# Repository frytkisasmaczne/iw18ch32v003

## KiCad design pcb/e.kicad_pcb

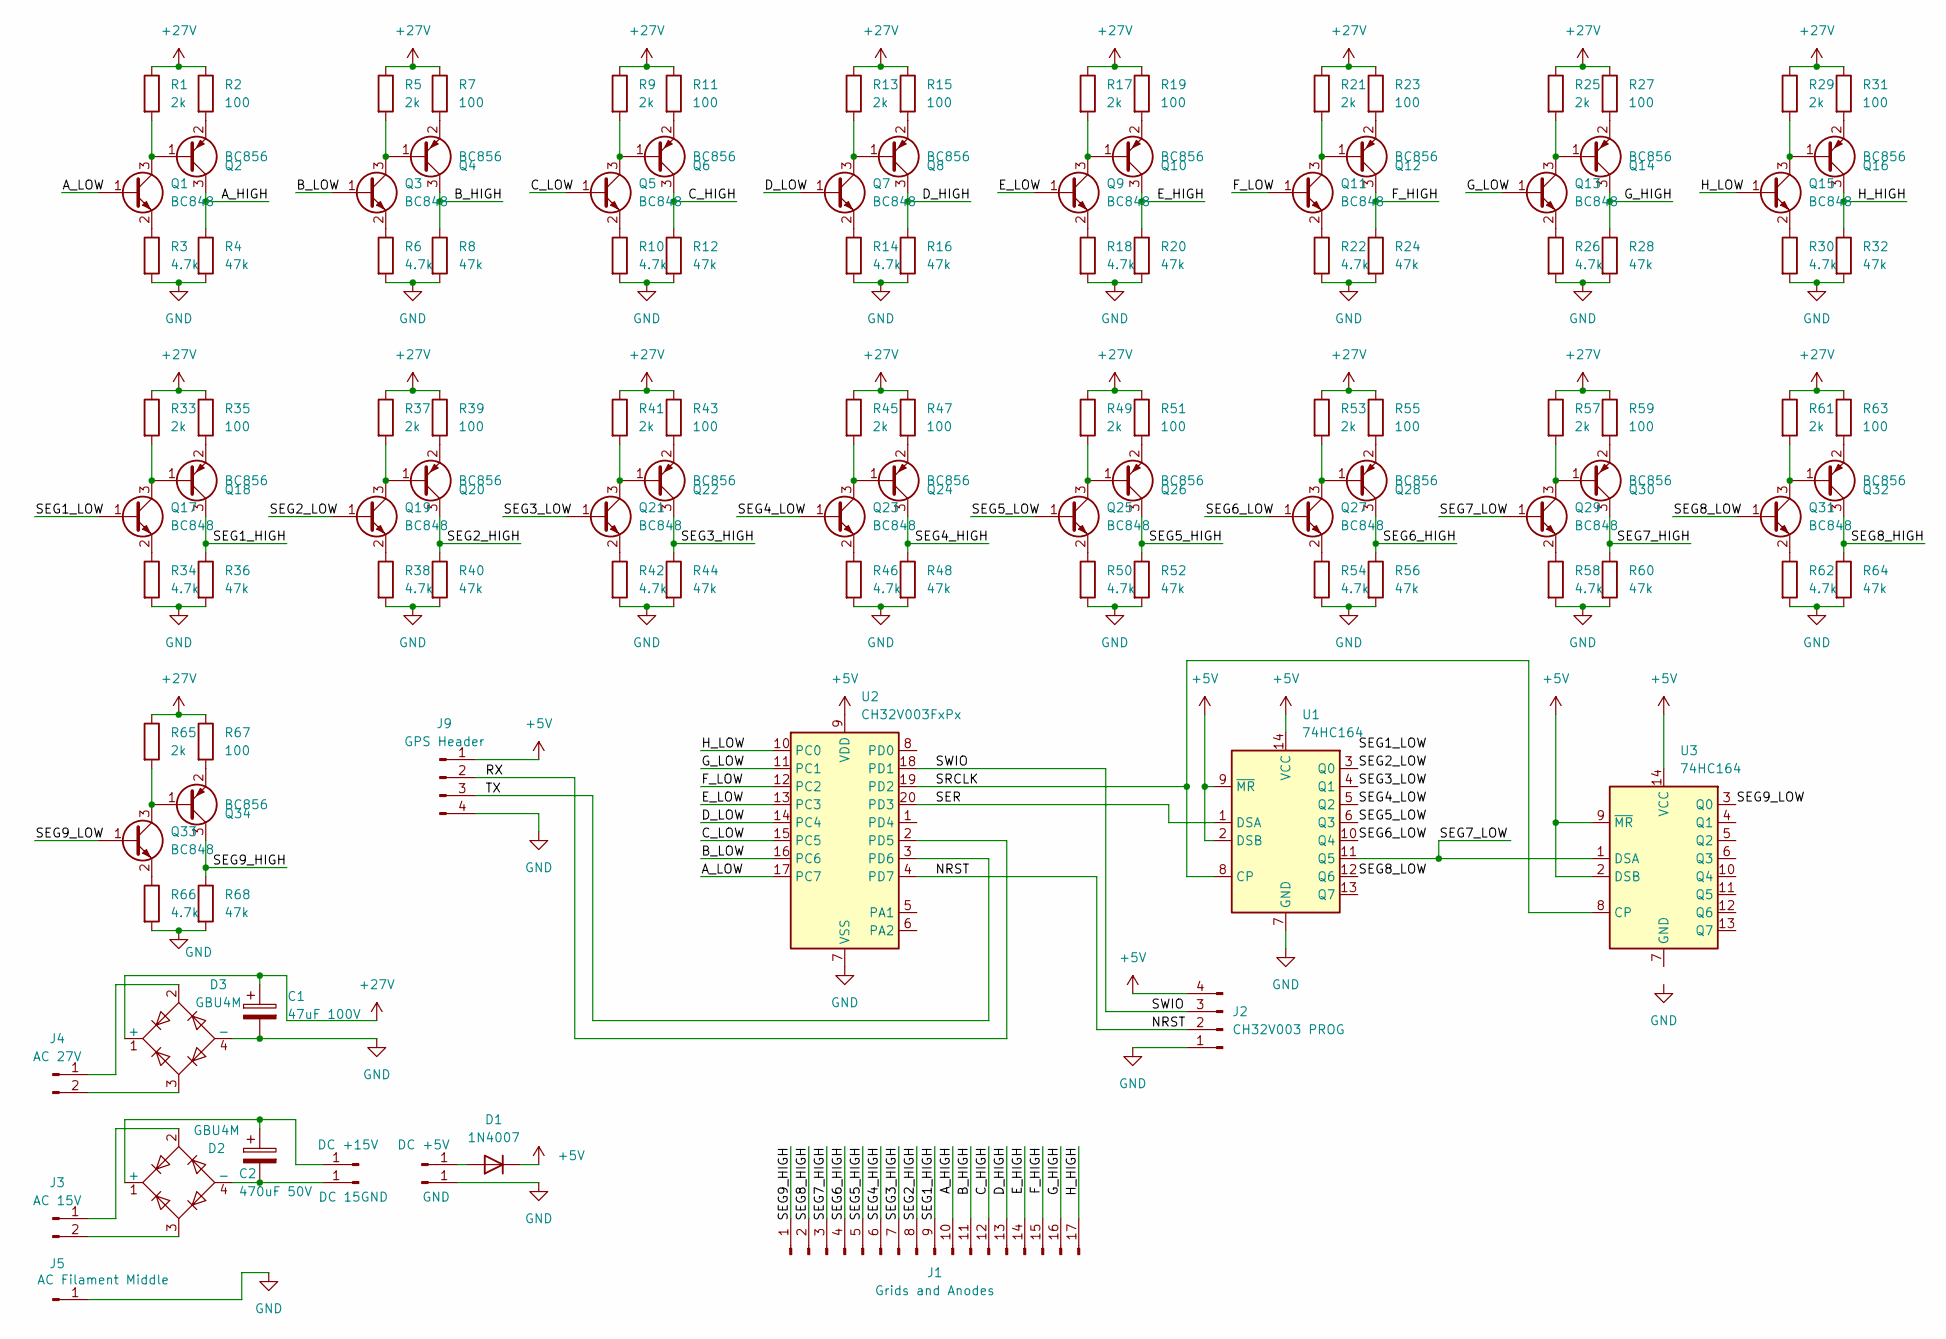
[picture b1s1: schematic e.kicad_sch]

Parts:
C1: 47uF 100V; CP_Radial_D10.0mm_P5.00mm
C2: 470uF 50V; CP_Radial_D13.0mm_P5.00mm
D1: 1N4007; D_DO-41_SOD81_P10.16mm_Horizontal
D2, D3: GBU4M; Diode_Bridge_Vishay_GBU
J1: Grids and Anodes; PinHeader_1x17_P2.54mm_Vertical
J2: CH32V003 PROG; PinHeader_1x04_P2.54mm_Vertical
J3: AC 15V; PinHeader_1x02_P2.54mm_Vertical
J4: AC 27V; PinHeader_1x02_P2.54mm_Vertical
J5: AC Filament Middle; PinHeader_1x01_P2.54mm_Vertical
J6: DC +15V; PinHeader_1x01_P2.54mm_Vertical
J7: DC 15GND; PinHeader_1x01_P2.54mm_Vertical
J8: DC +5V; PinHeader_1x01_P2.54mm_Vertical
J9: GPS Header; PinHeader_1x04_P2.54mm_Vertical
J10: GND; PinHeader_1x01_P2.54mm_Vertical
Q1, Q3, Q5, Q7, Q9, Q11, Q13, Q15, Q17, Q19, Q21, Q23, Q25, Q27, Q29, Q31, Q33: BC848; SOT-23
Q2, Q4, Q6, Q8, Q10, Q12, Q14, Q16, Q18, Q20, Q22, Q24, Q26, Q28, Q30, Q32, Q34: BC856; SOT-23
R1, R5, R9, R13, R17, R21, R25, R29, R33, R37, R41, R45, R49, R53, R57, R61, R65: 2k; R_0201_0603Metric
R2, R7, R11, R15, R19, R23, R27, R31, R35, R39, R43, R47, R51, R55, R59, R63, R67: 100; R_0201_0603Metric
R3, R6, R10, R14, R18, R22, R26, R30, R34, R38, R42, R46, R50, R54, R58, R62, R66: 4.7k; R_0201_0603Metric
R4, R8, R12, R16, R20, R24, R28, R32, R36, R40, R44, R48, R52, R56, R60, R64, R68: 47k; R_0201_0603Metric
U1, U3: 74HC164; SSOP-14_5.3x6.2mm_P0.65mm
U2: CH32V003FxPx; TSSOP-20_4.4x6.5mm_P0.65mm

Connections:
+5V: D1.1 (K), J2.4, J9.1, U1.2 (DSB), U1.9 (~MR), U1.14 (VCC), U2.9 (VDD), U3.2 (DSB), U3.9 (~MR), U3.14 (VCC)
+27V: C1.1, D3.1 (+), R1.1, R2.1, R5.1, R7.1, R9.1, R11.1, R13.1, R15.1, R17.1, R19.1, R21.1, R23.1, R25.1, R27.1, R29.1, R31.1, R33.1, R35.1, R37.1, R39.1, R41.1, R43.1, R45.1, R47.1, R49.1, R51.1, R53.1, R55.1, R57.1, R59.1, R61.1, R63.1, R65.1, R67.1
/A_HIGH: J1.10, Q2.3 (C), R4.1
/A_LOW: Q1.1 (B), U2.17 (PC7)
/B_HIGH: J1.11, Q4.3 (C), R8.1
/B_LOW: Q3.1 (B), U2.16 (PC6)
/C_HIGH: J1.12, Q6.3 (C), R12.1
/C_LOW: Q5.1 (B), U2.15 (PC5)
/D_HIGH: J1.13, Q8.3 (C), R16.1
/D_LOW: Q7.1 (B), U2.14 (PC4)
/E_HIGH: J1.14, Q10.3 (C), R20.1
/E_LOW: Q9.1 (B), U2.13 (PC3)
/F_HIGH: J1.15, Q12.3 (C), R24.1
/F_LOW: Q11.1 (B), U2.12 (PC2)
/G_HIGH: J1.16, Q14.3 (C), R28.1
/G_LOW: Q13.1 (B), U2.11 (PC1)
/H_HIGH: J1.17, Q16.3 (C), R32.1
/H_LOW: Q15.1 (B), U2.10 (PC0)
/NRST: J2.2, U2.4 (PD7)
/RX: J9.2, U2.2 (PD5)
/SEG1_HIGH: J1.9, Q18.3 (C), R36.1
/SEG1_LOW: Q17.1 (B)
/SEG2_HIGH: J1.8, Q20.3 (C), R40.1
/SEG2_LOW: Q19.1 (B), U1.3 (Q0)
/SEG3_HIGH: J1.7, Q22.3 (C), R44.1
/SEG3_LOW: Q21.1 (B), U1.4 (Q1)
/SEG4_HIGH: J1.6, Q24.3 (C), R48.1
/SEG4_LOW: Q23.1 (B), U1.5 (Q2)
/SEG5_HIGH: J1.5, Q26.3 (C), R52.1
/SEG5_LOW: Q25.1 (B), U1.6 (Q3)
/SEG6_HIGH: J1.4, Q28.3 (C), R56.1
/SEG6_LOW: Q27.1 (B), U1.10 (Q4)
/SEG7_HIGH: J1.3, Q30.3 (C), R60.1
/SEG7_LOW: Q29.1 (B), U1.11 (Q5), U3.1 (DSA)
/SEG8_HIGH: J1.2, Q32.3 (C), R64.1
/SEG8_LOW: Q31.1 (B), U1.12 (Q6)
/SEG9_HIGH: J1.1, Q34.3 (C), R68.1
/SEG9_LOW: Q33.1 (B), U3.3 (Q0)
/SER: U1.1 (DSA), U2.20 (PD3)
/SRCLK: U1.8 (CP), U2.19 (PD2), U3.8 (CP)
/SWIO: J2.3, U2.18 (PD1)
/TX: J9.3, U2.3 (PD6)
GND: C1.2, D3.4 (-), J2.1, J5.1, J9.4, J10.1, R3.2, R4.2, R6.2, R8.2, R10.2, R12.2, R14.2, R16.2, R18.2, R20.2, R22.2, R24.2, R26.2, R28.2, R30.2, R32.2, R34.2, R36.2, R38.2, R40.2, R42.2, R44.2, R46.2, R48.2, R50.2, R52.2, R54.2, R56.2, R58.2, R60.2, R62.2, R64.2, R66.2, R68.2, U1.7 (GND), U2.7 (VSS)
unnamed: D1.2 (A), J8.1
unnamed: C2.1, D2.1 (+), J6.1
unnamed: C2.2, D2.4 (-), J7.1
unnamed: D2.2, J3.1
unnamed: D2.3, J3.2
unnamed: D3.2, J4.1
unnamed: D3.3, J4.2
unnamed: Q1.3 (C), Q2.1 (B), R1.2
unnamed: Q1.2 (E), R3.1
unnamed: Q2.2 (E), R2.2
unnamed: Q3.3 (C), Q4.1 (B), R5.2
unnamed: Q3.2 (E), R6.1
unnamed: Q4.2 (E), R7.2
unnamed: Q5.3 (C), Q6.1 (B), R9.2
unnamed: Q5.2 (E), R10.1
unnamed: Q6.2 (E), R11.2
unnamed: Q7.3 (C), Q8.1 (B), R13.2
unnamed: Q7.2 (E), R14.1
unnamed: Q8.2 (E), R15.2
unnamed: Q9.2 (E), R18.1
unnamed: Q9.3 (C), Q10.1 (B), R17.2
unnamed: Q10.2 (E), R19.2
unnamed: Q11.3 (C), Q12.1 (B), R21.2
unnamed: Q11.2 (E), R22.1
unnamed: Q12.2 (E), R23.2
unnamed: Q13.3 (C), Q14.1 (B), R25.2
unnamed: Q13.2 (E), R26.1
unnamed: Q14.2 (E), R27.2
unnamed: Q15.3 (C), Q16.1 (B), R29.2
unnamed: Q15.2 (E), R30.1
unnamed: Q16.2 (E), R31.2
unnamed: Q17.3 (C), Q18.1 (B), R33.2
unnamed: Q17.2 (E), R34.1
unnamed: Q18.2 (E), R35.2
unnamed: Q19.3 (C), Q20.1 (B), R37.2
unnamed: Q19.2 (E), R38.1
unnamed: Q20.2 (E), R39.2
unnamed: Q21.3 (C), Q22.1 (B), R41.2
unnamed: Q21.2 (E), R42.1
unnamed: Q22.2 (E), R43.2
unnamed: Q23.3 (C), Q24.1 (B), R45.2
unnamed: Q23.2 (E), R46.1
unnamed: Q24.2 (E), R47.2
unnamed: Q25.3 (C), Q26.1 (B), R49.2
unnamed: Q25.2 (E), R50.1
unnamed: Q26.2 (E), R51.2
unnamed: Q27.3 (C), Q28.1 (B), R53.2
unnamed: Q27.2 (E), R54.1
unnamed: Q28.2 (E), R55.2
unnamed: Q29.3 (C), Q30.1 (B), R57.2
unnamed: Q29.2 (E), R58.1
unnamed: Q30.2 (E), R59.2
unnamed: Q31.3 (C), Q32.1 (B), R61.2
unnamed: Q31.2 (E), R62.1
unnamed: Q32.2 (E), R63.2
unnamed: Q33.3 (C), Q34.1 (B), R65.2
unnamed: Q33.2 (E), R66.1
unnamed: Q34.2 (E), R67.2

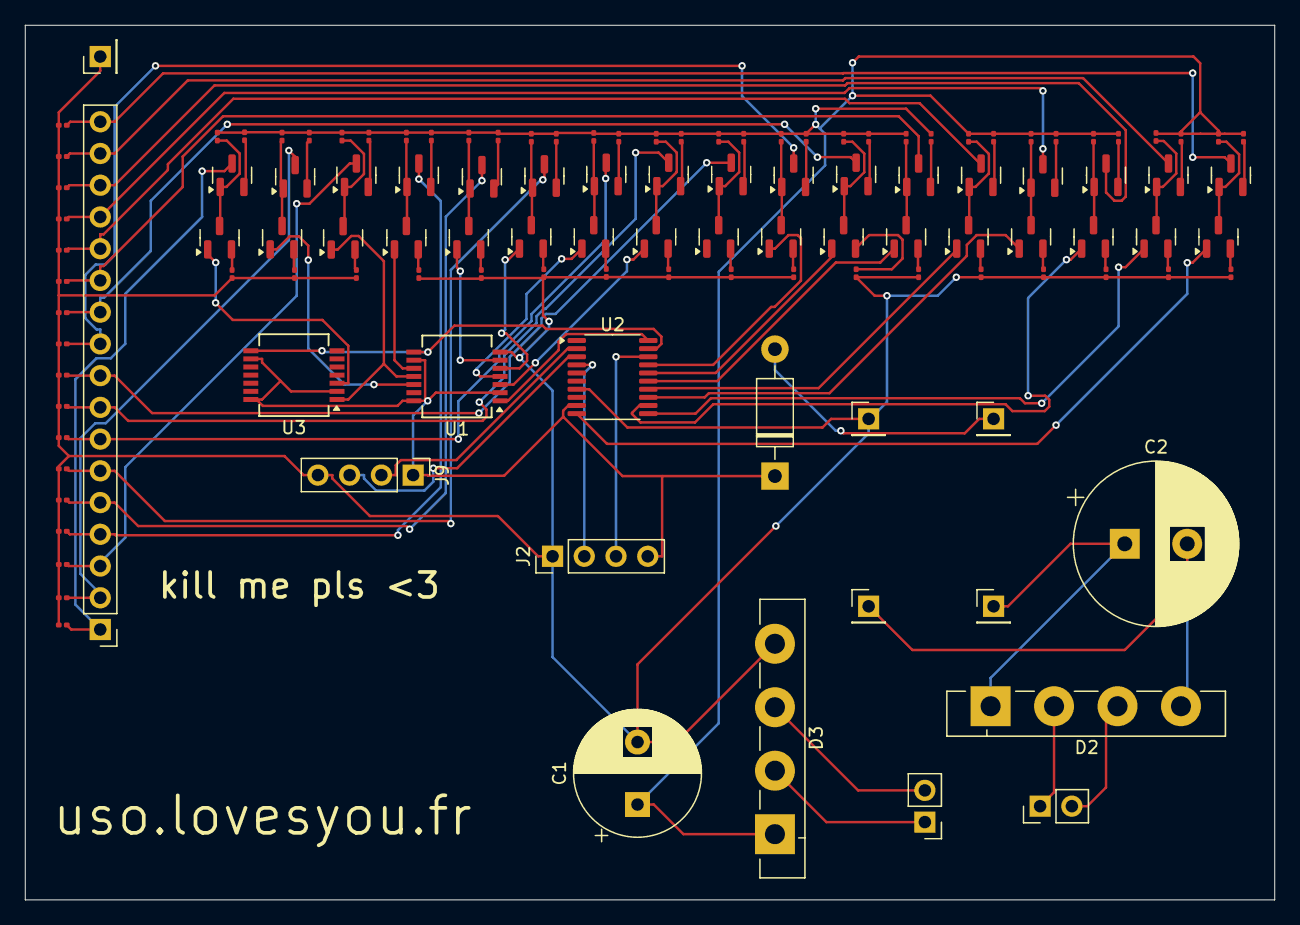
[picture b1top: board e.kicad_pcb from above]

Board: 2 copper layers, 100.0 x 70.0 mm, 120 parts (0 on the bottom side), 100 nets.

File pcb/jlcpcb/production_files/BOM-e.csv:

Comment,Designator,Footprint,LCSC,Quantity
GND,J10,PinHeader_1x01_P2.54mm_Vertical,,1
DC +5V,J8,PinHeader_1x01_P2.54mm_Vertical,,1
DC 15GND,J7,PinHeader_1x01_P2.54mm_Vertical,,1
DC +15V,J6,PinHeader_1x01_P2.54mm_Vertical,,1
BC848,Q13,SOT-23,,1
BC856,Q20,SOT-23,,1
BC848,Q23,SOT-23,,1
470uF 50V,C2,CP_Radial_D13.0mm_P5.00mm,,1
4.7k,R62,R_0201_0603Metric,,1
100,R23,R_0201_0603Metric,,1
47k,R40,R_0201_0603Metric,,1
100,R51,R_0201_0603Metric,,1
100,R11,R_0201_0603Metric,,1
2k,R13,R_0201_0603Metric,,1
BC848,Q31,SOT-23,,1
BC848,Q7,SOT-23,,1
BC856,Q30,SOT-23,,1
4.7k,R58,R_0201_0603Metric,,1
4.7k,R3,R_0201_0603Metric,,1
BC856,Q6,SOT-23,,1
Grids and Anodes,J1,PinHeader_1x17_P2.54mm_Vertical,,1
74HC164,U3,SSOP-14_5.3x6.2mm_P0.65mm,,1
GPS Header,J9,PinHeader_1x04_P2.54mm_Vertical,,1
100,R55,R_0201_0603Metric,,1
47k,R56,R_0201_0603Metric,,1
4.7k,R38,R_0201_0603Metric,,1
4.7k,R34,R_0201_0603Metric,,1
BC856,Q8,SOT-23,,1
4.7k,R14,R_0201_0603Metric,,1
BC848,Q33,SOT-23,,1
2k,R21,R_0201_0603Metric,,1
2k,R41,R_0201_0603Metric,,1
BC848,Q15,SOT-23,,1
4.7k,R6,R_0201_0603Metric,,1
2k,R9,R_0201_0603Metric,,1
AC 15V,J3,PinHeader_1x02_P2.54mm_Vertical,,1
BC856,Q22,SOT-23,,1
BC856,Q16,SOT-23,,1
2k,R37,R_0201_0603Metric,,1
BC848,Q1,SOT-23,,1
BC856,Q26,SOT-23,,1
4.7k,R10,R_0201_0603Metric,,1
47k,R60,R_0201_0603Metric,,1
CH32V003 PROG,J2,PinHeader_1x04_P2.54mm_Vertical,,1
BC856,Q4,SOT-23,,1
BC848,Q9,SOT-23,,1
BC856,Q32,SOT-23,,1
2k,R5,R_0201_0603Metric,,1
BC848,Q19,SOT-23,,1
2k,R1,R_0201_0603Metric,,1
100,R39,R_0201_0603Metric,,1
47k,R28,R_0201_0603Metric,,1
4.7k,R42,R_0201_0603Metric,,1
100,R19,R_0201_0603Metric,,1
BC856,Q12,SOT-23,,1
47k,R36,R_0201_0603Metric,,1
BC856,Q34,SOT-23,,1
100,R59,R_0201_0603Metric,,1
2k,R33,R_0201_0603Metric,,1
2k,R25,R_0201_0603Metric,,1
100,R31,R_0201_0603Metric,,1
4.7k,R22,R_0201_0603Metric,,1
100,R15,R_0201_0603Metric,,1
47k,R16,R_0201_0603Metric,,1
47k,R68,R_0201_0603Metric,,1
4.7k,R50,R_0201_0603Metric,,1
4.7k,R30,R_0201_0603Metric,,1
100,R67,R_0201_0603Metric,,1
100,R7,R_0201_0603Metric,,1
47k,R48,R_0201_0603Metric,,1
100,R27,R_0201_0603Metric,,1
BC856,Q28,SOT-23,,1
47k,R20,R_0201_0603Metric,,1
47k,R8,R_0201_0603Metric,,1
BC856,Q24,SOT-23,,1
AC Filament Middle,J5,PinHeader_1x01_P2.54mm_Vertical,,1
2k,R65,R_0201_0603Metric,,1
100,R2,R_0201_0603Metric,,1
47k,R32,R_0201_0603Metric,,1
BC848,Q5,SOT-23,,1
1N4007,D1,D_DO-41_SOD81_P10.16mm_Horizontal,,1
BC848,Q29,SOT-23,,1
47k,R52,R_0201_0603Metric,,1
100,R43,R_0201_0603Metric,,1
47k,R4,R_0201_0603Metric,,1
2k,R61,R_0201_0603Metric,,1
2k,R49,R_0201_0603Metric,,1
47k,R44,R_0201_0603Metric,,1
BC848,Q25,SOT-23,,1
100,R63,R_0201_0603Metric,,1
100,R47,R_0201_0603Metric,,1
47uF 100V,C1,CP_Radial_D10.0mm_P5.00mm,,1
BC848,Q11,SOT-23,,1
AC 27V,J4,PinHeader_1x02_P2.54mm_Vertical,,1
BC856,Q18,SOT-23,,1
74HC164,U1,SSOP-14_5.3x6.2mm_P0.65mm,,1
BC848,Q17,SOT-23,,1
2k,R53,R_0201_0603Metric,,1
4.7k,R54,R_0201_0603Metric,,1
CH32V003FxPx,U2,TSSOP-20_4.4x6.5mm_P0.65mm,,1
2k,R17,R_0201_0603Metric,,1
BC856,Q2,SOT-23,,1
4.7k,R18,R_0201_0603Metric,,1
47k,R12,R_0201_0603Metric,,1
2k,R57,R_0201_0603Metric,,1
4.7k,R26,R_0201_0603Metric,,1
BC848,Q21,SOT-23,,1
BC848,Q3,SOT-23,,1
2k,R29,R_0201_0603Metric,,1
BC856,Q10,SOT-23,,1
GBU4M,D2,Diode_Bridge_Vishay_GBU,,1
BC856,Q14,SOT-23,,1
4.7k,R46,R_0201_0603Metric,,1
4.7k,R66,R_0201_0603Metric,,1
100,R35,R_0201_0603Metric,,1
2k,R45,R_0201_0603Metric,,1
47k,R24,R_0201_0603Metric,,1
BC848,Q27,SOT-23,,1
47k,R64,R_0201_0603Metric,,1
GBU4M,D3,Diode_Bridge_Vishay_GBU,,1

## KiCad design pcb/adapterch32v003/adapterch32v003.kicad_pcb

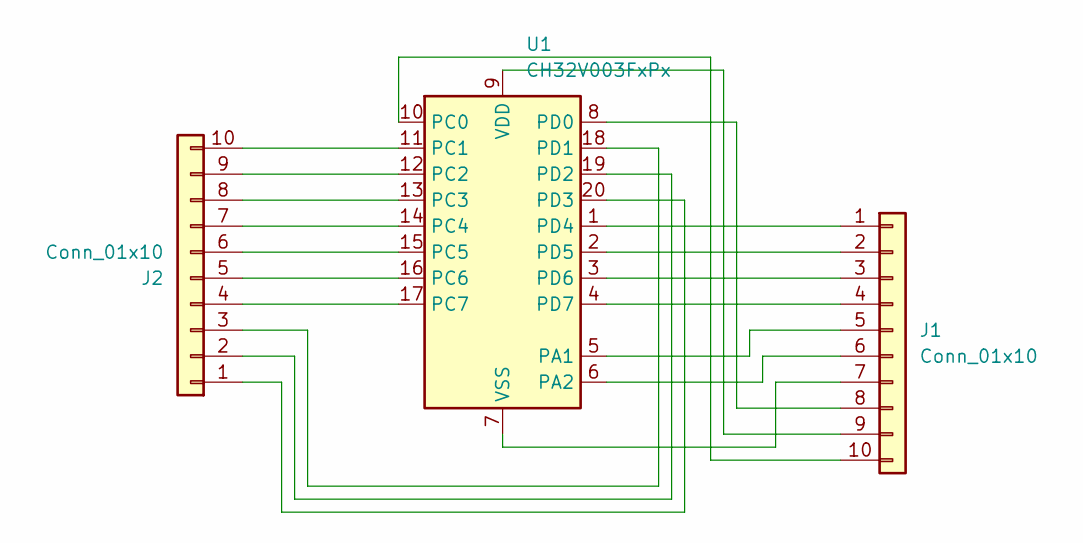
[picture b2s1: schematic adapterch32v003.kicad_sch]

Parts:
J1, J2: Conn_01x10; PinHeader_1x10_P2.54mm_Vertical
U1: CH32V003FxPx; TSSOP-20_4.4x6.5mm_P0.65mm

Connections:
unnamed: J1.1, U1.1 (PD4)
unnamed: J1.2, U1.2 (PD5)
unnamed: J1.3, U1.3 (PD6)
unnamed: J1.4, U1.4 (PD7)
unnamed: J1.5, U1.5 (PA1)
unnamed: J1.6, U1.6 (PA2)
unnamed: J1.7, U1.7 (VSS)
unnamed: J1.8, U1.8 (PD0)
unnamed: J1.9, U1.9 (VDD)
unnamed: J1.10, U1.10 (PC0)
unnamed: J2.1, U1.20 (PD3)
unnamed: J2.2, U1.19 (PD2)
unnamed: J2.3, U1.18 (PD1)
unnamed: J2.4, U1.17 (PC7)
unnamed: J2.5, U1.16 (PC6)
unnamed: J2.6, U1.15 (PC5)
unnamed: J2.7, U1.14 (PC4)
unnamed: J2.8, U1.13 (PC3)
unnamed: J2.9, U1.12 (PC2)
unnamed: J2.10, U1.11 (PC1)

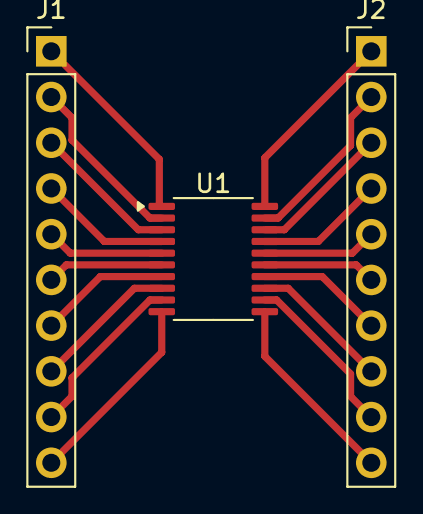
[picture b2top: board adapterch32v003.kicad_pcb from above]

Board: 2 copper layers, 3 parts (0 on the bottom side), 20 nets.

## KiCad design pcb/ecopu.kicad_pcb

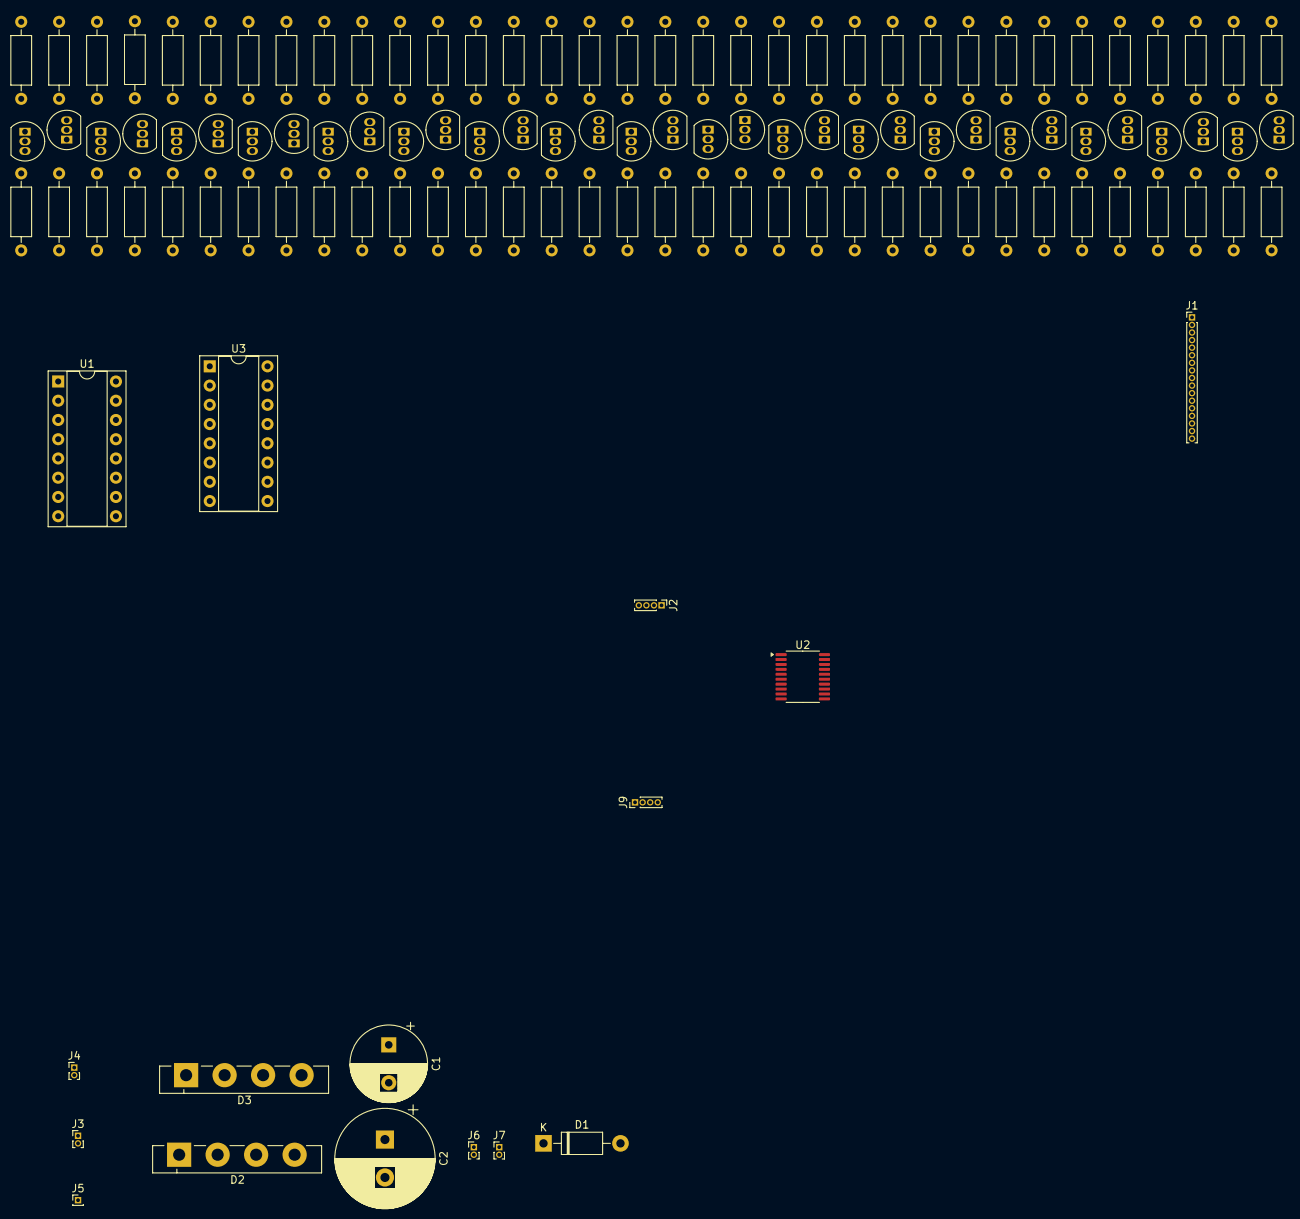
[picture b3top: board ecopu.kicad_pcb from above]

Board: 2 copper layers, 118 parts (0 on the bottom side), 101 nets, no tracks yet.

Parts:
C1: 47uF 100V; CP_Radial_D10.0mm_P5.00mm
C2: 470uF 50V; CP_Radial_D13.0mm_P5.00mm
D1: 1N4007; D_DO-41_SOD81_P10.16mm_Horizontal
D2, D3: GBU4M; Diode_Bridge_Vishay_GBU
J1: Grids and Anodes; PinHeader_1x17_P1.00mm_Vertical
J2: CH32V003 PROG; PinHeader_1x04_P1.00mm_Vertical
J3: AC 15V; PinHeader_1x02_P1.00mm_Vertical
J4: AC 27V; PinHeader_1x02_P1.00mm_Vertical
J5: AC Filament Middle; PinHeader_1x01_P1.00mm_Vertical
J6: Step-down IN; PinHeader_1x02_P1.00mm_Vertical
J7: Step-down OUT; PinHeader_1x02_P1.00mm_Vertical
J9: GPS Header; PinHeader_1x04_P1.00mm_Vertical
Q1, Q3, Q5, Q7, Q9, Q11, Q13, Q15, Q17, Q19, Q21, Q23, Q25, Q27, Q29, Q31, Q33: BC237; TO-92_Inline
Q2, Q4, Q6, Q8, Q10, Q12, Q14, Q16, Q18, Q20, Q22, Q24, Q26, Q28, Q30, Q32, Q34: BC307; TO-92_Inline
R1, R5, R9, R13, R17, R21, R25, R29, R33, R37, R41, R45, R49, R53, R57, R61, R65: 2k; R_Axial_DIN0207_L6.3mm_D2.5mm_P10.16mm_Horizontal
R2, R7, R11, R15, R19, R23, R27, R31, R35, R39, R43, R47, R51, R55, R59, R63, R67: 100; R_Axial_DIN0207_L6.3mm_D2.5mm_P10.16mm_Horizontal
R3, R6, R10, R14, R18, R22, R26, R30, R34, R38, R42, R46, R50, R54, R58, R62, R66: 4.7k; R_Axial_DIN0207_L6.3mm_D2.5mm_P10.16mm_Horizontal
R4, R8, R12, R16, R20, R24, R28, R32, R36, R40, R44, R48, R52, R56, R60, R64, R68: 47k; R_Axial_DIN0207_L6.3mm_D2.5mm_P10.16mm_Horizontal
U1, U3: 74HC595; DIP-16_W7.62mm_Socket
U2: CH32V003FxPx; TSSOP-20_4.4x6.5mm_P0.65mm

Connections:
+3.3V: D1.1 (K), U1.16 (VCC), U2.9 (VDD), U3.16 (VCC)
+5V: J2.4, J9.1, U1.10 (~SRCLR), U3.10 (~SRCLR)
+27V: C1.1, D3.1 (+), R1.1, R2.1, R5.1, R7.1, R9.1, R11.1, R13.1, R15.1, R17.1, R19.1, R21.1, R23.1, R25.1, R27.1, R29.1, R31.1, R33.1, R35.1, R37.1, R39.1, R41.1, R43.1, R45.1, R47.1, R49.1, R51.1, R53.1, R55.1, R57.1, R59.1, R61.1, R63.1, R65.1, R67.1
/A_HIGH: J1.10, Q2.1 (C), R4.1
/A_LOW: Q1.2 (B), U2.17 (PC7)
/B_HIGH: J1.11, Q4.1 (C), R8.1
/B_LOW: Q3.2 (B), U2.16 (PC6)
/C_HIGH: J1.12, Q6.1 (C), R12.1
/C_LOW: Q5.2 (B), U2.15 (PC5)
/D_HIGH: J1.13, Q8.1 (C), R16.1
/D_LOW: Q7.2 (B), U2.14 (PC4)
/E_HIGH: J1.14, Q10.1 (C), R20.1
/E_LOW: Q9.2 (B), U2.13 (PC3)
/F_HIGH: J1.15, Q12.1 (C), R24.1
/F_LOW: Q11.2 (B), U2.12 (PC2)
/G_HIGH: J1.16, Q14.1 (C), R28.1
/G_LOW: Q13.2 (B), U2.11 (PC1)
/H_HIGH: J1.17, Q16.1 (C), R32.1
/H_LOW: Q15.2 (B), U2.10 (PC0)
/NRST: J2.2, U2.4 (PD7)
/RX: J9.2, U2.2 (PD5)
/SEG1_HIGH: J1.9, Q18.1 (C), Q20.1 (C), R36.1, R40.1
/SEG1_LOW: Q17.2 (B), U1.15 (QA)
/SEG2_LOW: Q19.2 (B), U1.1 (QB)
/SEG3_HIGH: J1.7, Q22.1 (C), R44.1
/SEG3_LOW: Q21.2 (B), U1.2 (QC)
/SEG4_HIGH: J1.6, Q24.1 (C), R48.1
/SEG4_LOW: Q23.2 (B), U1.3 (QD)
/SEG5_HIGH: J1.5, Q26.1 (C), R52.1
/SEG5_LOW: Q25.2 (B), U1.4 (QE)
/SEG6_HIGH: J1.4, Q28.1 (C), R56.1
/SEG6_LOW: Q27.2 (B), U1.5 (QF)
/SEG7_HIGH: J1.3, Q30.1 (C), R60.1
/SEG7_LOW: Q29.2 (B), U1.6 (QG), U3.14 (SER)
/SEG8_HIGH: J1.2, Q32.1 (C), R64.1
/SEG8_LOW: Q31.2 (B), U1.7 (QH)
/SEG9_HIGH: J1.1, Q34.1 (C), R68.1
/SEG9_LOW: Q33.2 (B), U3.15 (QA)
/SER: U1.14 (SER), U2.20 (PD3)
/SRCLK: U1.11 (SRCLK), U1.12 (RCLK), U2.19 (PD2), U3.11 (SRCLK), U3.12 (RCLK)
/SWIO: J2.3, U2.18 (PD1)
/TX: J9.3, U2.3 (PD6)
GND: C1.2, D3.4 (-), J2.1, J5.1, J7.2, J9.4, R3.2, R4.2, R6.2, R8.2, R10.2, R12.2, R14.2, R16.2, R18.2, R20.2, R22.2, R24.2, R26.2, R28.2, R30.2, R32.2, R34.2, R36.2, R38.2, R40.2, R42.2, R44.2, R46.2, R48.2, R50.2, R52.2, R54.2, R56.2, R58.2, R60.2, R62.2, R64.2, R66.2, R68.2, U1.8 (GND), U1.13 (~OE), U2.7 (VSS), U3.8 (GND), U3.13 (~OE)
unnamed: D1.2 (A), J7.1
unnamed: C2.1, D2.1 (+), J6.2
unnamed: C2.2, D2.4 (-), J6.1
unnamed: D2.2, J3.1
unnamed: D2.3, J3.2
unnamed: D3.2, J4.1
unnamed: D3.3, J4.2
unnamed: Q1.1 (C), Q2.2 (B), R1.2
unnamed: Q1.3 (E), R3.1
unnamed: Q2.3 (E), R2.2
unnamed: Q3.1 (C), Q4.2 (B), R5.2
unnamed: Q3.3 (E), R6.1
unnamed: Q4.3 (E), R7.2
unnamed: Q5.1 (C), Q6.2 (B), R9.2
unnamed: Q5.3 (E), R10.1
unnamed: Q6.3 (E), R11.2
unnamed: Q7.1 (C), Q8.2 (B), R13.2
unnamed: Q7.3 (E), R14.1
unnamed: Q8.3 (E), R15.2
unnamed: Q9.3 (E), R18.1
unnamed: Q9.1 (C), Q10.2 (B), R17.2
unnamed: Q10.3 (E), R19.2
unnamed: Q11.1 (C), Q12.2 (B), R21.2
unnamed: Q11.3 (E), R22.1
unnamed: Q12.3 (E), R23.2
unnamed: Q13.1 (C), Q14.2 (B), R25.2
unnamed: Q13.3 (E), R26.1
unnamed: Q14.3 (E), R27.2
unnamed: Q15.1 (C), Q16.2 (B), R29.2
unnamed: Q15.3 (E), R30.1
unnamed: Q16.3 (E), R31.2
unnamed: Q17.1 (C), Q18.2 (B), R33.2
unnamed: Q17.3 (E), R34.1
unnamed: Q18.3 (E), R35.2
unnamed: Q19.1 (C), Q20.2 (B), R37.2
unnamed: Q19.3 (E), R38.1
unnamed: Q20.3 (E), R39.2
unnamed: Q21.1 (C), Q22.2 (B), R41.2
unnamed: Q21.3 (E), R42.1
unnamed: Q22.3 (E), R43.2
unnamed: Q23.1 (C), Q24.2 (B), R45.2
unnamed: Q23.3 (E), R46.1
unnamed: Q24.3 (E), R47.2
unnamed: Q25.1 (C), Q26.2 (B), R49.2
unnamed: Q25.3 (E), R50.1
unnamed: Q26.3 (E), R51.2
unnamed: Q27.1 (C), Q28.2 (B), R53.2
unnamed: Q27.3 (E), R54.1
unnamed: Q28.3 (E), R55.2
unnamed: Q29.1 (C), Q30.2 (B), R57.2
unnamed: Q29.3 (E), R58.1
unnamed: Q30.3 (E), R59.2
unnamed: Q31.1 (C), Q32.2 (B), R61.2
unnamed: Q31.3 (E), R62.1
unnamed: Q32.3 (E), R63.2
unnamed: Q33.1 (C), Q34.2 (B), R65.2
unnamed: Q33.3 (E), R66.1
unnamed: Q34.3 (E), R67.2

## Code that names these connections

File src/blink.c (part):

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// };

// const int segments[12] = {
// 	PC2,PD4,PD3,PD2,PD0,PC7,PC6,PC5,PC0, /* seg a-h */
// 	PC3,PC4,PC1, /* SRCLK, SER, OE */
// };
const int segments[12] = {
	PC0,PC1,PC2,PC3,PC4,PC5,PC6,PC7, /* seg a-h */
	PD2,PD3, /* SRCLK, SER */
};

const uint8_t sevensegmap[13] = {
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	// 		for (uint8_t i = 0; i < 8; i++) {
	// 			if ( (sevensegmap[ digits[idig] ] >> i) & 1 )
	// 			{
	// 				// funDigitalWrite(PC4, 1);
	// 				bDigitalWrite(10, 1);
	// 			} else
	// 			{
	// 				// funDigitalWrite(PC4, 0);
	// 				bDigitalWrite(10, 0);
	// 			}
	// 			// funDigitalWrite(PC3, 1);
	// 			bDigitalWrite(9, 1);
	// 			// Delay_Us( 1 );
	// 			// funDigitalWrite(PC3, 0);
	// 			bDigitalWrite(9, 0);
	// 			// Delay_Us( 1 );
	// 			// Delay_Ms( 10 );
	// 		}
	// 		// funDigitalWrite(PC3, 1);
	// 		bDigitalWrite(9, 1);
	// 		// Delay_Us( 1 );
	// 		// funDigitalWrite(PC3, 0);
	// 		bDigitalWrite(9, 0);


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
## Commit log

2025-02-07 smd pcb
